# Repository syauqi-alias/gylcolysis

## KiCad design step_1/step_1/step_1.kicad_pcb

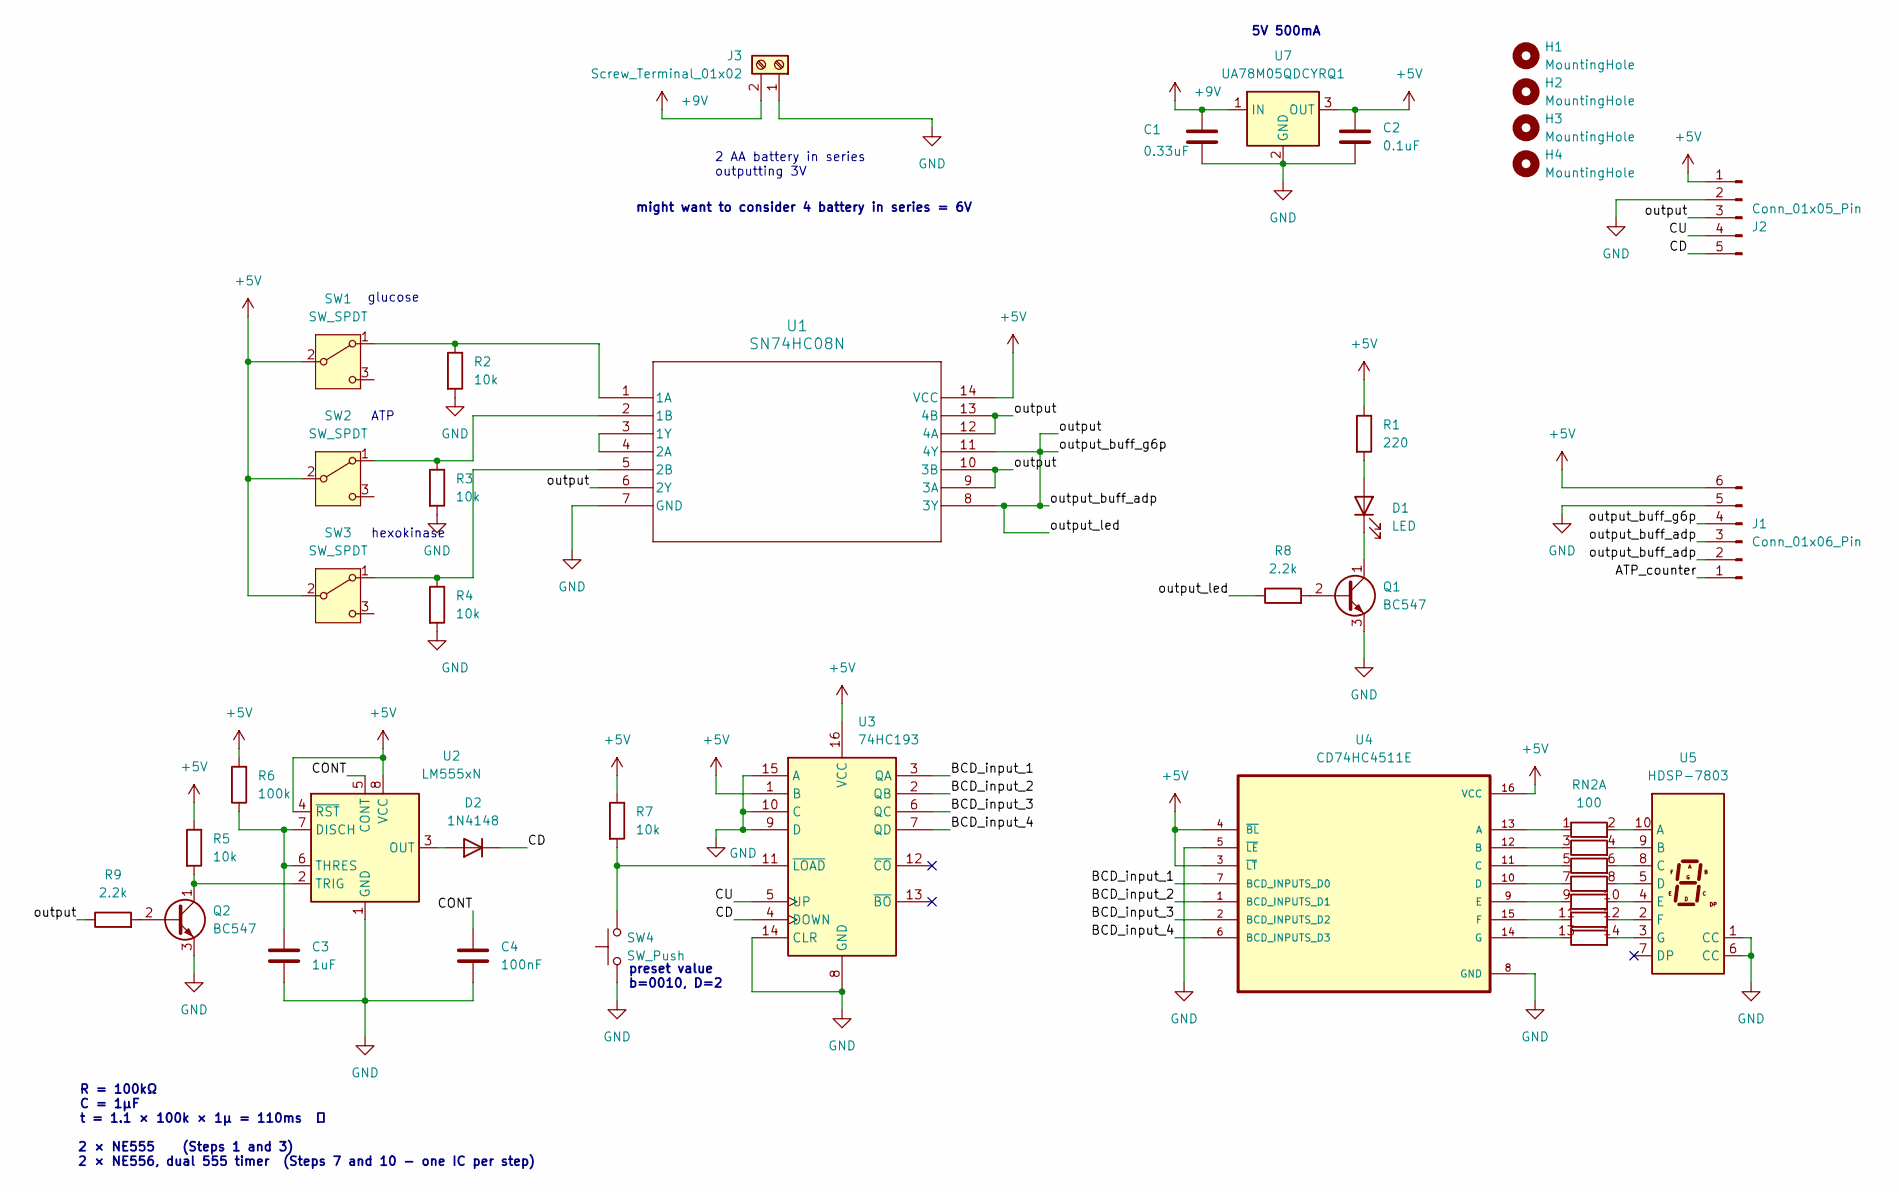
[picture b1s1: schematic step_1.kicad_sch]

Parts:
C1: 0.33uF; C_Disc_D10.0mm_W2.5mm_P5.00mm; mouser 810-FA28X7R1H334KRU6
C2: 0.1uF; C_Disc_D10.0mm_W2.5mm_P5.00mm; mouser 810-FG28X7R1H104KNT0
C3: 1uF; C_Disc_D10.0mm_W2.5mm_P5.00mm; mouser 810-FG24X7R1H105KRT6
C4: 100nF; C_Disc_D10.0mm_W2.5mm_P5.00mm; mouser 810-FG28X7R1H104KNT0
D1: LED; LED_D5.0mm; mouser 696-SSLLX5093GD125
D2: 1N4148; D_DO-35_SOD27_P7.62mm_Horizontal; mouser 512-1N4148TA
H1, H2, H3, H4: MountingHole; MountingHole_2.7mm_M2.5_DIN965
J1: Conn_01x06_Pin; Harwin_M20-89006xx_1x06_P2.54mm_Horizontal
J2: Conn_01x05_Pin; PinHeader_1x05_P2.54mm_Horizontal; mouser 649-1012937990501BLF
J3: Screw_Terminal_01x02; Altech_AK100_1x02_P5.00mm; mouser 845-30.002
Q1, Q2: BC547; TO-92_Inline; mouser 637-BC547B
R1: 220; R_Axial_DIN0207_L6.3mm_D2.5mm_P10.16mm_Horizontal; mouser 603-CFR-25JT-52-220R
R2, R3, R4, R5, R7: 10k; R_Axial_DIN0207_L6.3mm_D2.5mm_P10.16mm_Horizontal; mouser 603-CFR-25JB-52-10K
R6: 100k; R_Axial_DIN0207_L6.3mm_D2.5mm_P10.16mm_Horizontal; mouser 603-CFR-25JT-52C100K
R8, R9: 2.2k; R_Axial_DIN0207_L6.3mm_D2.5mm_P10.16mm_Horizontal; mouser 603-CFR-25JT-52-220R
RN2: 100; R_Array_SIP14; mouser 652-4614X-2LF-100
SW1, SW2, SW3: SW_SPDT; SW_Slide-03_Wuerth-WS-SLTV_10x2.5x6.4_P2.54mm; mouser 179-SLW1166415ASD
SW4: SW_Push; SW_PUSH_6mm_H4.3mm; mouser 179-TS026643BK160LCR
U1: SN74HC08N; DIP-14_W7.62mm_LongPads; mouser 595-SN74HC08N
U2: LM555xN; DIP-8_W7.62mm; mouser 926-LM555CN/NOPB
U3: 74HC193; DIP-16_W7.62mm_LongPads; mouser 595-CD74HC193E
U4: CD74HC4511E; DIP-16_W7.62mm_LongPads; mouser 595-CD74HC4511E
U5: HDSP-7803; HDSP-7801; mouser 859-LSHD-7803
U7: UA78M05QDCYRQ1; TO-220-3_Horizontal_TabDown; mouser 595-UA78M05IKCSE3

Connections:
+5V: C2.1, J1.6, J2.1, R1.1, R5.1, R6.2, R7.1, SW1.2 (B), SW2.2 (B), SW3.2 (B), U1.14 (VCC), U2.4 (~RST), U2.8 (VCC), U3.1 (B), U3.16 (VCC), U4.3 (~LT), U4.4 (~BL), U4.16 (VCC), U7.3 (OUT)
+9V: C1.1, J3.2, U7.1 (IN)
/BCD_input_1: U3.3 (QA), U4.7 (BCD_INPUTS_D0)
/BCD_input_2: U3.2 (QB), U4.1 (BCD_INPUTS_D1)
/BCD_input_3: U3.6 (QC), U4.2 (BCD_INPUTS_D2)
/BCD_input_4: U3.7 (QD), U4.6 (BCD_INPUTS_D3)
/CD: D2.1 (K), J2.5, U3.4 (DOWN)
/CONT: C4.1, U2.5 (CONT)
/CU: J2.4, U3.5 (UP)
/output: J1.2, J1.3, J1.4, J2.3, R8.1, R9.1, U1.6 (2Y), U1.8 (3Y), U1.9 (3A), U1.10 (3B), U1.11 (4Y), U1.12 (4A), U1.13 (4B)
GND: C1.2, C2.2, C3.2, C4.2, J1.5, J2.2, J3.1, Q1.3 (E), Q2.3 (E), R2.2, R3.2, R4.2, SW4.1, U1.7 (GND), U2.1 (GND), U3.8 (GND), U3.9 (D), U3.10 (C), U3.14 (CLR), U3.15 (A), U4.5 (~LE), U4.8 (GND), U5.1 (CC), U5.6 (CC), U7.2 (GND)
unnamed: D1.2 (A), R1.2
unnamed: D1.1 (K), Q1.1 (C)
unnamed: D2.2 (A), U2.3 (OUT)
unnamed: Q1.2 (B), R8.2
unnamed: Q2.2 (B), R9.2
unnamed: Q2.1 (C), R5.2, U2.2 (TRIG)
unnamed: RN2.1 (R1.1), U4.13 (A)
unnamed: RN2.2 (R1.2), U5.10 (A)
unnamed: RN2.3 (R2.1), U4.12 (B)
unnamed: RN2.4 (R2.2), U5.9 (B)
unnamed: RN2.5 (R3.1), U4.11 (C)
unnamed: RN2.6 (R3.2), U5.8 (C)
unnamed: RN2.7 (R4.1), U4.10 (D)
unnamed: RN2.8 (R4.2), U5.5 (D)
unnamed: RN2.9 (R5.1), U4.9 (E)
unnamed: RN2.10 (R5.2), U5.4 (E)
unnamed: RN2.11 (R6.1), U4.15 (F)
unnamed: RN2.12 (R6.2), U5.2 (F)
unnamed: RN2.13 (R7.1), U4.14 (G)
unnamed: RN2.14 (R7.2), U5.3 (G)
unnamed: R2.1, SW1.1 (A), U1.1 (1A)
unnamed: R3.1, SW2.1 (A), U1.2 (1B)
unnamed: R4.1, SW3.1 (A), U1.5 (2B)
unnamed: U1.3 (1Y), U1.4 (2A)
unnamed: C3.1, R6.1, U2.6 (THRES), U2.7 (DISCH)
unnamed: R7.2, SW4.2, U3.11 (~LOAD)

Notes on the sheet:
2 × NE555 (Steps 1 and 3) 2 × NE556, dual 555 timer (Steps 7 and 10 - one IC per step)
5V 500mA
glucose
hexokinase
preset value b=0010, D=2
R = 100kΩ C = 1µF t = 1.1 × 100k × 1µ = 110ms ✓
2 AA battery in series outputting 3V
ATP
might want to consider 4 battery in series = 6V

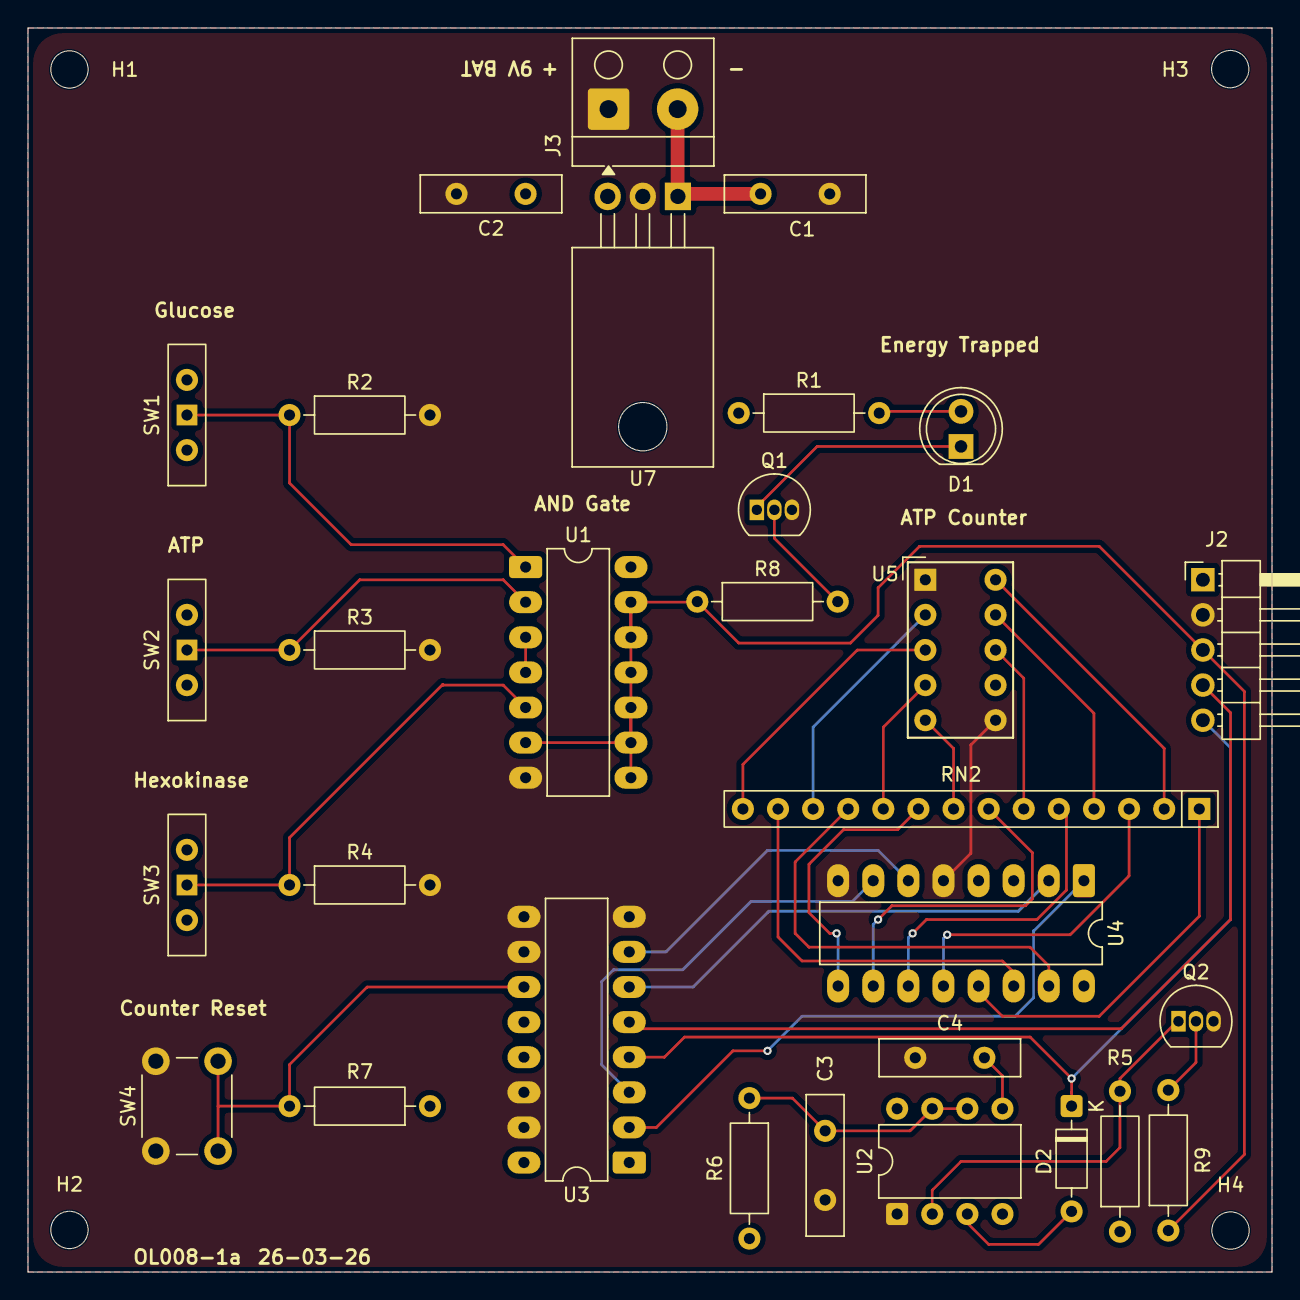
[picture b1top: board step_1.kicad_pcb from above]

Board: 2 copper layers, 90.0 x 90.0 mm, 34 parts (0 on the bottom side), 37 nets.

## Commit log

2026-06-11 name change
